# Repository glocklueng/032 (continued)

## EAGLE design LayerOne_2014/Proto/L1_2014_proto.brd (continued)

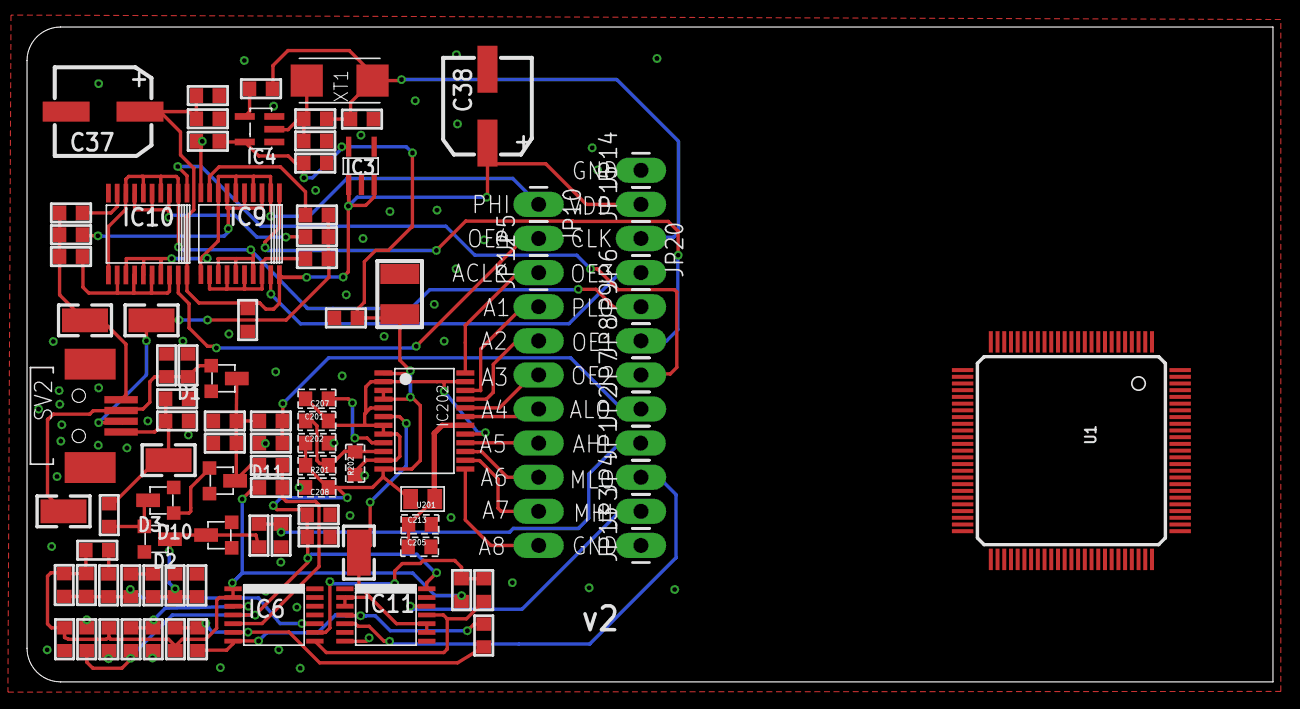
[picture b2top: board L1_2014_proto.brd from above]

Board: 2 copper layers, 92.8 x 48.8 mm, 97 parts (1 on the bottom side), 53 nets.

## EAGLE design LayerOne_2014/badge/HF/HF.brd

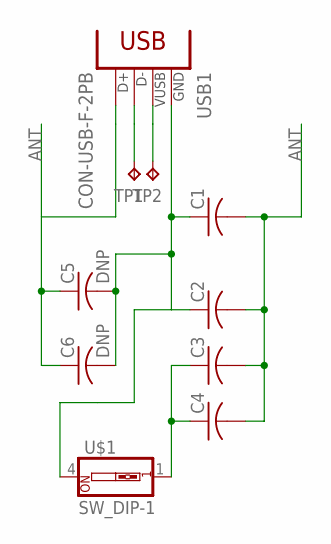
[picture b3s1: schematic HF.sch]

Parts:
C1, C2, C3, C4: C-USC1206; C1206
C5, C6: DNP; C1206
TP1, TP2: TPPAD1-13; P1-13
U$1: SW_DIP-1; DIPSWITCH-01
USB1: CON-USB-F-2PB; CONN_USB_A_F

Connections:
ANT: C1.2, C2.2, C3.2, C4.2, C5.1, C6.1, USB1.3 (D+)
unnamed: C1.1, C2.1, C5.2, C6.2, U$1.4, USB1.4 (GND)
unnamed: C3.1, C4.1, U$1.1
unnamed: TP1.TP, USB1.2 (D-)
unnamed: TP2.TP, USB1.1 (VUSB)

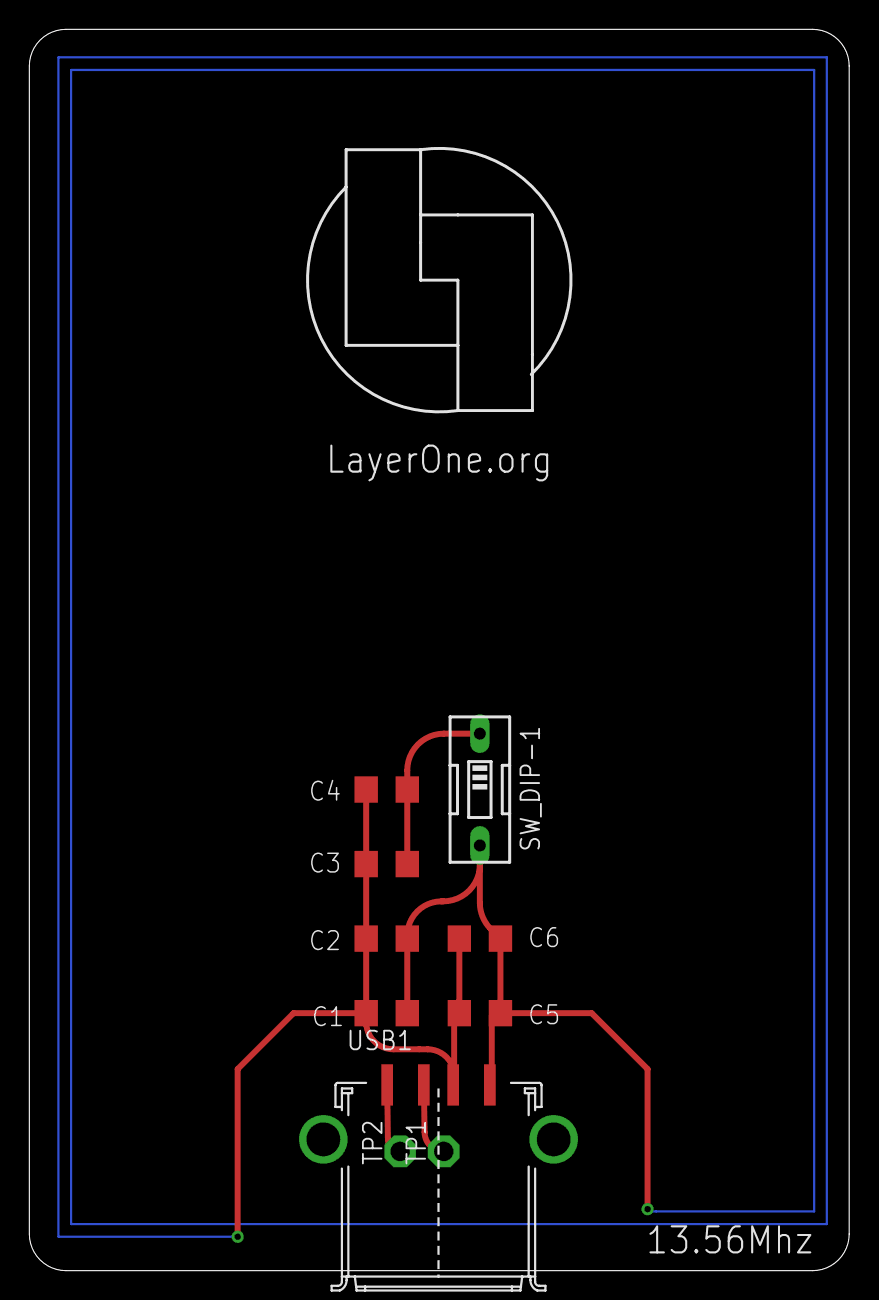
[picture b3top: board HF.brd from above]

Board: 2 copper layers, 55.9 x 84.6 mm, 11 parts (0 on the bottom side), 5 nets.

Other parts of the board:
U$2: LARGE_L1_LOGO

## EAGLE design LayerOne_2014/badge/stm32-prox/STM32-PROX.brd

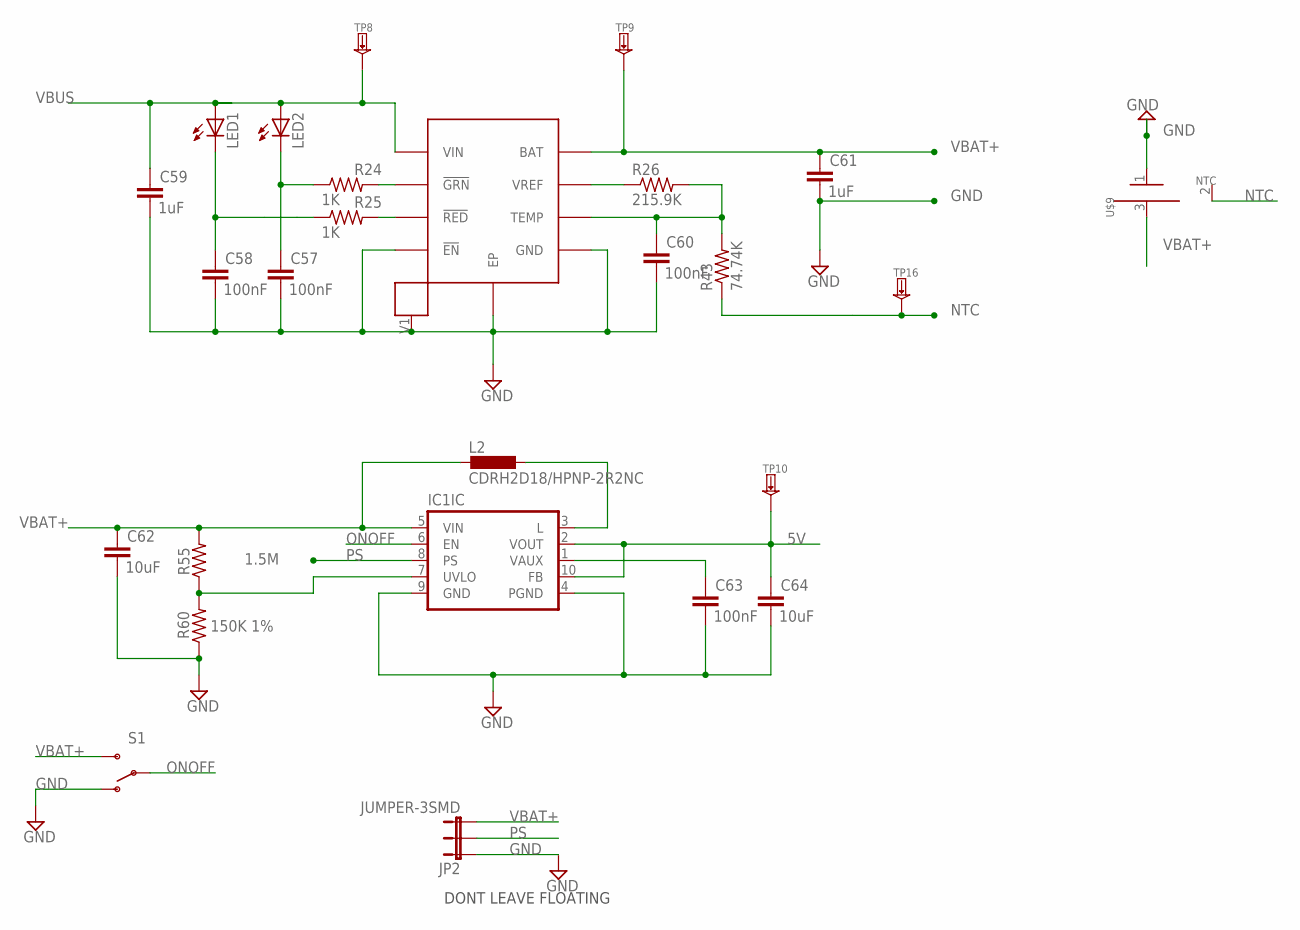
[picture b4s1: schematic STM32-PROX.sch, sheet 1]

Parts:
C57, C58, C60, C63: 100nF; RLC_0603; MPN CL10B104KO8NNNC; DIGIKEY 1276-1005-1-ND
C59, C61: 1uF; RLC_0603; MPN CC0603ZRY5V7BB105; DIGIKEY 311-1372-1-ND
C62, C64: 10uF; RLC_0603; MPN C1608X5R1C106M080AB; DIGIKEY 445-9065-1-ND
IC1: IC_TPS6120XQFN10; QFN-10; MPN TPS61202DRCT; DIGIKEY 296-21685-1-ND
JP2: JUMPER-3SMD; SJ_3; MPN NONE
L2: CDRH2D18/HPNP-2R2NC; CDRH2D18; PARTNO *
LED1: LED_LEDSML0603; LED_SML0603; PARTNO *; DIGIKEY 475-1409-1-ND
LED2: LED_LEDSML0603; LED_SML0603; PARTNO *; DIGIKEY 475-3016-1-ND
R24, R25: 1K; RLC_0603; MPN RMCF0603JT1K00; DIGIKEY RMCF0603JT1K00CT-ND
R26: 215.9K; RLC_0603; MPN CRCW0603215KFKEA; DIGIKEY 541-215KHCT-ND
R43: 74.74K; RLC_0603; MPN RMCF0603JT75K0; DIGIKEY RMCF0603JT75K0CT-ND
R55: 1.5M; RLC_0603; TOLERANCE 5%; MPN ESR03EZPJ155; DIGIKEY RHM1.5MDCT-ND
R60: 150K 1%; RLC_0603; TOLERANCE 1%; MPN ESR03EZPF1503; DIGIKEY RHM150KADCT-ND
S1: SWITCH-SPDT-SMD-A; SWITCH-SPST-SMD-A; PARTNO *
TP8: TESTPADKEYSTONE-SMD; SMD-TESTPOINT; MPN NONE
TP9, TP10: TESTPADKEYSTONE-SMD; --MERGED_KEYSTONE-SMD-TESTPOINT-5015; MPN NONE
TP16: TESTPAD; SMD-TESTPOINT
U$7: MC34674; UDFN-EP; MPN MC34674AEPR2; DIGIKEY MC34674AEPR2TR-ND
U$9: BATT; MPN MC34674AEPR2; DIGIKEY MC34674AEPR2TR-ND

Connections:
5V: C64.1, IC1.2 (VOUT), IC1.10 (FB), TP10.1; also elsewhere on the board
GND: C57.2, C58.2, C59.2, C60.2, C61.2, C62.2, C63.2, C64.2, IC1.4 (PGND), IC1.9 (GND), IC1.P0 (GND), IC1.P1 (GND), IC1.P2 (GND), IC1.P3 (GND), IC1.P4 (GND), IC1.V0 (GND), IC1.V1 (GND), JP2.1, R60.1, S1.1 (O), U$7.4 (!EN), U$7.5 (GND), U$7.9 (EP), U$7.V1, U$9.1 (NEG); also elsewhere on the board
unnamed: C57.1, LED2.C, R24.1
unnamed: R24.2, U$7.2 (!GRN)
unnamed: C58.1, LED1.C, R25.1
unnamed: R25.2, U$7.3 (!RED)
unnamed: R26.1, U$7.7 (VREF)
unnamed: C60.1, R26.2, R43.2, U$7.6 (TEMP)
unnamed: C63.1, IC1.1 (VAUX)
unnamed: IC1.7 (UVLO), R55.1, R60.2
unnamed: IC1.3 (L), L2.P$2 (2)
NTC: R43.1, TP16.1, U$9.2 (NTC)
ONOFF: IC1.6 (EN), S1.2
PS: IC1.8 (PS), JP2.2
VBAT+: C61.1, C62.1, IC1.5 (VIN), JP2.3, L2.P$1 (1), R55.2, S1.3 (S), TP9.1, U$7.8 (BAT), U$9.3 (POS)
VBUS: C59.1, LED1.A, LED2.A, TP8.1, U$7.1 (VIN); also elsewhere on the board

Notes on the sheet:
DONT LEAVE FLOATING

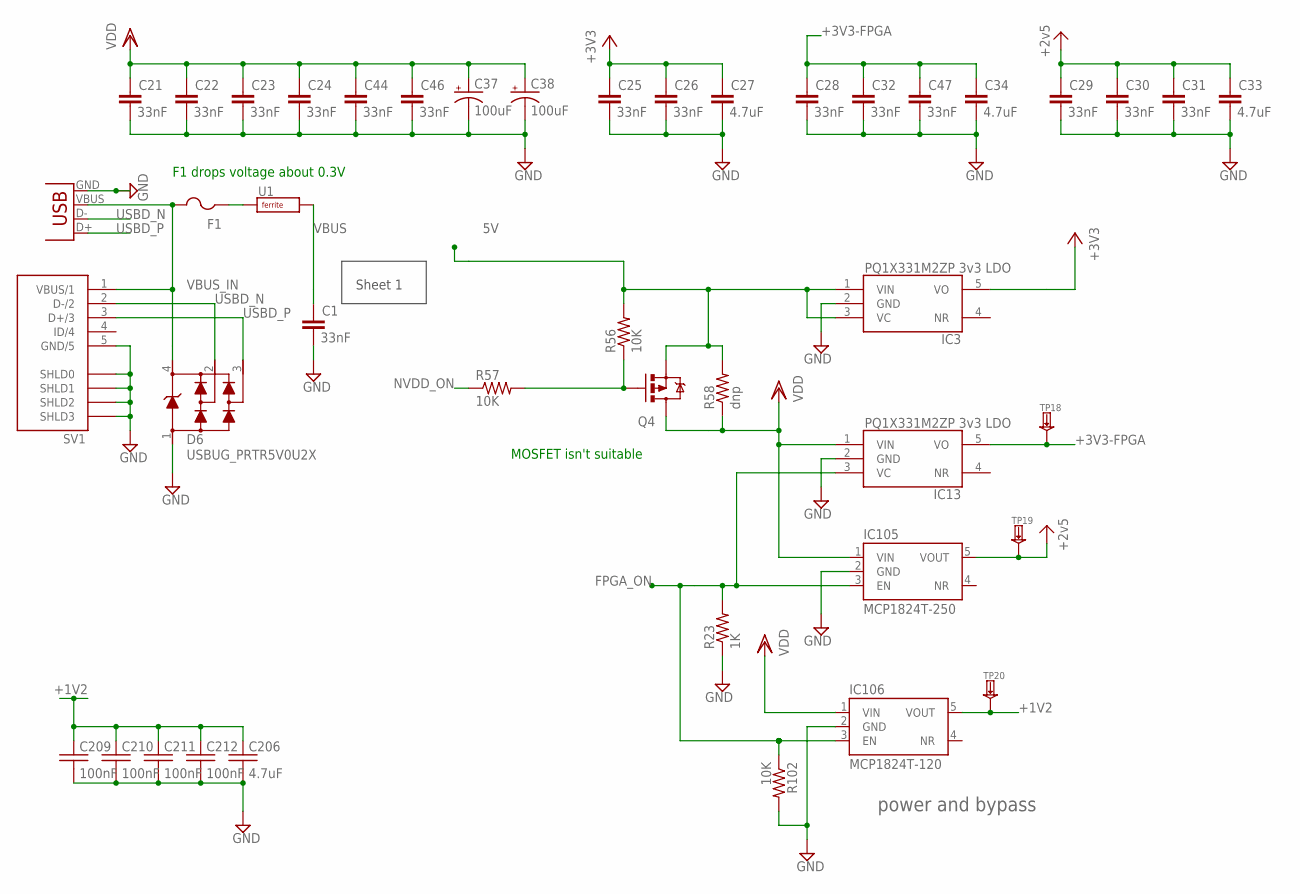
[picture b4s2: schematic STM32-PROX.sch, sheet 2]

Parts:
C1, C21, C22, C23, C24, C25, C26, C28, C29, C30, C31, C32, C44, C46, C47: 33nF; RLC_0603; MPN CC0603KRX7R9BB333; DIGIKEY 311-1429-1-ND
C27, C33, C34: 4.7uF; RLC_1210; MPN CL32B475KOINNNE; DIGIKEY 1276-1856-1-ND
C37, C38: 100uF; D/7343-31R; MPN T491D107K010AT; DIGIKEY 399-3769-1-ND
C206: 4.7uF; RLC_0603; MPN EMK107ABJ475KA-T; DIGIKEY 1276-1784-1-ND
C209, C210, C211, C212: 100nF; RLC_0603; MPN CL10B104KO8NNNC; DIGIKEY 1276-1005-1-ND
D6: USBUG_PRTR5V0U2X; USBUG_SOT143B
F1: PTCFUSE-1812; 1812; MPN MICROSMD050F-2; DIGIKEY MICROSMD050FCT-ND
IC3: PQ1X331M2ZP-3V3-LDO-SOT-23-5; SOT-23-5; MPN LP2985-33DBVR; DIGIKEY 296-18476-1-ND
IC13: PQ1X331M2ZP-3V3-LDO-SOT-23-5; SOT-23-5; MPN LP2985-33DBVR; DIGIKEY 296-18476-2-ND
IC105: MCP1824T-250; SOT-23-5; MPN MCP1824T-2502E/OT; DIGIKEY MCP1824T-2502E/OTCT-ND
IC106: MCP1824T-120; SOT-23-5; MPN MCP1824T-1202E/OT; DIGIKEY MCP1824T-1202E/OTCT-ND
Q4: MOSFET-PCHANNELSMD; SOT23-3; MPN SI2303CDS-T1-GE3; DIGIKEY SI2303CDS-T1-GE3CT-ND
R23: 1K; RLC_0603; MPN RMCF0603JT1K00; DIGIKEY RMCF0603JT1K00CT-ND
R56, R57, R102: 10K; RLC_0603; MPN RMCF0603JT10K0; DIGIKEY RMCF0603JT10K0CT-ND
R58: dnp; RLC_0603; PARTNO *
SV1: USB-MINIB; USB-MINIB-SMD; PARTNO *
TP18, TP19, TP20: TESTPAD; SMD-TESTPOINT
U1: FERRITE0805; RLC_0805; MPN MPZ2012S300A; DIGIKEY 445-1566-1-ND
USB-MICRO: USB-MICROB; MPN 1981568-1; DIGIKEY A97800CT-ND

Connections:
5V: IC3.1 (VIN), IC3.3 (VC), Q4.2 (S), R56.2, R58.2; also elsewhere on the board
+1V2: C206.1, C209.1, C210.1, C211.1, C212.1, IC106.5 (VOUT), TP20.1; also elsewhere on the board
+2V5: C29.1, C30.1, C31.1, C33.1, IC105.5 (VOUT), TP19.1; also elsewhere on the board
+3V3-FPGA: C28.1, C32.1, C34.1, C47.1, IC13.5 (VO), TP18.1; also elsewhere on the board
FPGA_ON: IC13.3 (VC), IC105.3 (EN), IC106.3 (EN), R23.2, R102.1; also elsewhere on the board
GND: C1.2, C21.2, C22.2, C23.2, C24.2, C25.2, C26.2, C27.2, C28.2, C29.2, C30.2, C31.2, C32.2, C33.2, C34.2, C37.-, C38.-, C44.2, C46.2, C47.2, C206.2, C209.2, C210.2, C211.2, C212.2, D6.1, IC3.2 (GND), IC13.2 (GND), IC105.2 (GND), IC106.2 (GND), R23.1, R102.2, SV1.5 (GND/5), SV1.TAB0 (SHLD0), SV1.TAB1 (SHLD1), SV1.TAB2 (SHLD2), SV1.TAB3 (SHLD3), USB-MICRO.GND; also elsewhere on the board
unnamed: F1.1, U1.1 (A)
NVDD_ON: R57.1; also elsewhere on the board
PFETGATE: Q4.1 (G), R56.1, R57.2
USBD_N: D6.2, SV1.2 (D-/2), USB-MICRO.D-; also elsewhere on the board
USBD_P: D6.3, SV1.3 (D+/3), USB-MICRO.D+; also elsewhere on the board
VBUS: C1.1, U1.2 (B); also elsewhere on the board
VBUS_IN: D6.4, F1.2, SV1.1 (VBUS/1), USB-MICRO.VBUS
VCC: C25.1, C26.1, C27.1, IC3.5 (VO); also elsewhere on the board
VDD: C21.1, C22.1, C23.1, C24.1, C37.+, C38.+, C44.1, C46.1, IC13.1 (VIN), IC105.1 (VIN), IC106.1 (VIN), Q4.3 (D), R58.1; also elsewhere on the board

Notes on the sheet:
power and bypass
Sheet 1
F1 drops voltage about 0.3V
MOSFET isn't suitable

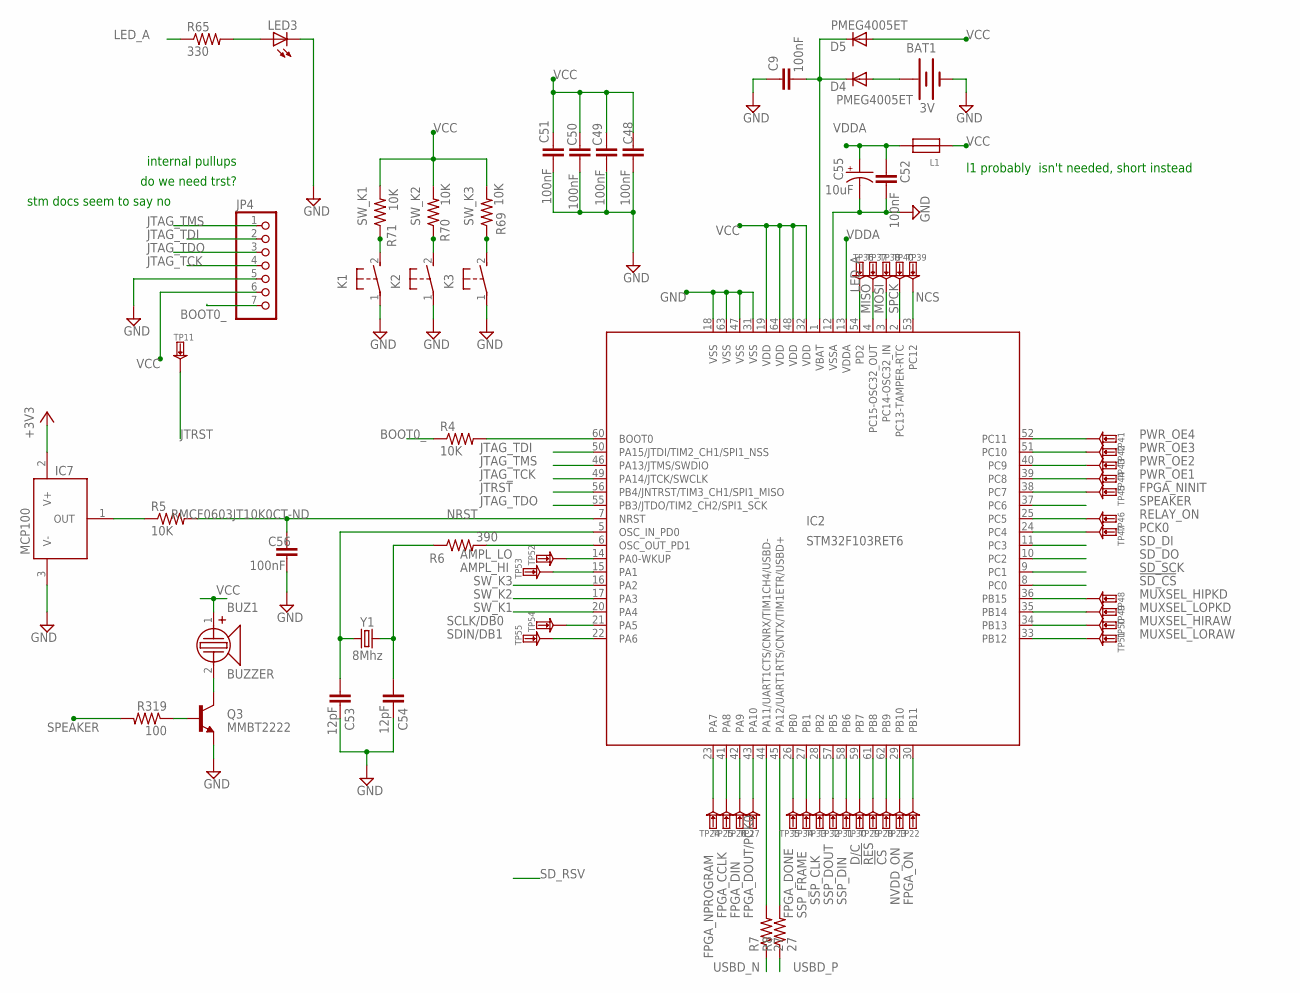
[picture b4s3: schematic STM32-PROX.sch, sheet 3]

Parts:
BAT1: 3V; NSL_SPARKFUN_BATTCON_12MM; MPN BK-885-TR; DIGIKEY BK-885CT-ND
BUZ1: BUZZER; MPN CCV-084B16; DIGIKEY 102-1265-1-ND
C9: 100nF; RLC_0603; MPN CL21F104ZBCNNNC; DIGIKEY 1276-1007-1-ND
C48, C49, C50, C51, C52, C56: 100nF; 0805; MPN CL21F104ZBCNNNC; DIGIKEY 1276-1007-1-ND
C53, C54: 12pF; 0805; MPN CL21C120JBANNNC; DIGIKEY 1276-1120-1-ND
C55: 10uF; EIA3216-KIT; MPN TAJA106M006RNJ; DIGIKEY 478-1656-1-ND
D4, D5: PMEG4005ET; SOT23-3; MPN PMEG4005ET,215; DIGIKEY 568-4134-1-ND
IC2: STM32F103RET6; LQFP64A_PACKAGE; MPN STM32F103RET6; DIGIKEY 497-6444-ND
IC7: MCP100; SOT23-3LEAD; MPN MCP100T-270I/TT; DIGIKEY MCP100T-270I/TTCT-ND
JP4: HEADER-1X7ROUND; 1X07_ROUND
K1, K2, K3: 5-XX; B3F-5XX; MPN PTS635SL50 LFS; DIGIKEY CKN9102-ND
L1: FERRITE1; 0603; MPN NONE
LED3: LED_LEDSML0603; LED_SML0603; PARTNO *; DIGIKEY 475-2558-1-ND
Q3: MMBT2222; SOT-23-3; MPN MMBT2222A-7-F
R4, R5, R69, R70, R71: 10K; RLC_0603; MPN RMCF0603JT10K0; DIGIKEY RMCF0603JT10K0CT-ND
R6: 390; RLC_0603; MPN RMCF0603JT390R; DIGIKEY RMCF0603JT390RCT-ND
R7, R8: 27; RLC_0603; MPN RMCF0603JT27R0; DIGIKEY RMCF0603JT27R0CT-ND
R65: 330; RLC_0603; MPN RMCF0603JT330R; DIGIKEY RMCF0603JT330RCT-ND
R319: 100; RLC_0603; MPN RMCF0603JT100R; DIGIKEY RMCF0603JT100RCT-ND
TP11, TP22, TP23, TP24, TP25, TP26, TP27, TP28, TP29, TP30, TP31, TP32, TP33, TP34, TP35, TP36, TP37, TP38, TP39, TP40, TP41, TP42, TP43, TP44, TP45, TP46, TP47, TP48, TP49, TP50, TP51, TP52, TP53, TP54, TP55: TESTPAD; SMD-TESTPOINT
Y1: 8Mhz; CRYSTAL-TXC-7A; MPN 7A-8.000MAAE-T; DIGIKEY 887-1740-1-ND

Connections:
!CS: IC2.62 (PB9), TP28.1; also elsewhere on the board
!RES: IC2.61 (PB8), TP29.1; also elsewhere on the board
!SD_CS: IC2.8 (PC0); also elsewhere on the board
AMPL_HI: IC2.15 (PA1), TP53.1; also elsewhere on the board
AMPL_LO: IC2.14 (PA0-WKUP), TP52.1; also elsewhere on the board
BOOT0: IC2.60 (BOOT0), R4.2
BOOT0_: JP4.7, R4.1
D/C: IC2.59 (PB7), TP30.1; also elsewhere on the board
D_N: IC2.44 (PA11/UART1CTS/CNRX/TIM1CH4/USBD-), R7.2
D_P: IC2.45 (PA12/UART1RTS/CNTX/TIM1ETR/USBD+), R8.2
FPGA_CCLK: IC2.41 (PA8), TP25.1; also elsewhere on the board
FPGA_DIN: IC2.42 (PA9), TP26.1; also elsewhere on the board
FPGA_DONE: IC2.26 (PB0), TP35.1; also elsewhere on the board
FPGA_DOUT/PCK0: IC2.43 (PA10), TP27.1; also elsewhere on the board
FPGA_NINIT: IC2.38 (PC7), TP45.1; also elsewhere on the board
FPGA_NPROGRAM: IC2.23 (PA7), TP24.1; also elsewhere on the board
FPGA_ON: IC2.30 (PB11), TP22.1; also elsewhere on the board
GND: BAT1.GND (-), C9.1, C48.2, C49.2, C50.2, C51.2, C52.2, C53.1, C54.1, C55.C (-), C56.2, IC2.12 (VSSA), IC2.18 (VSS), IC2.31 (VSS), IC2.47 (VSS), IC2.63 (VSS), IC7.3 (V-), JP4.5, K1.1, K2.1, K3.1, LED3.C, Q3.2 (E); also elsewhere on the board
JTAG_TCK: IC2.49 (PA14/JTCK/SWCLK), JP4.4
JTAG_TDI: IC2.50 (PA15/JTDI/TIM2_CH1/SPI1_NSS), JP4.2
JTAG_TDO: IC2.55 (PB3/JTDO/TIM2_CH2/SPI1_SCK), JP4.3
JTAG_TMS: IC2.46 (PA13/JTMS/SWDIO), JP4.1
JTRST: IC2.56 (PB4/JNTRST/TIM3_CH1/SPI1_MISO), TP11.1
LED3: LED3.A, R65.2
LED_A: IC2.54 (PD2), R65.1, TP36.1
MISO: IC2.4 (PC15-OSC32_OUT), TP37.1; also elsewhere on the board
MOSI: IC2.3 (PC14-OSC32_IN), TP38.1; also elsewhere on the board
MUXSEL_HIPKD: IC2.36 (PB15), TP48.1; also elsewhere on the board
MUXSEL_HIRAW: IC2.34 (PB13), TP50.1; also elsewhere on the board
MUXSEL_LOPKD: IC2.35 (PB14), TP49.1; also elsewhere on the board
MUXSEL_LORAW: IC2.33 (PB12), TP51.1; also elsewhere on the board
unnamed: C53.2, IC2.5 (OSC_IN_PD0), Y1.P$1 (1)
unnamed: C9.2, D4.3 (C), D5.3 (C), IC2.1 (VBAT)
unnamed: BAT1.PWR@1 (+), D4.1 (A)
unnamed: BUZ1.2, Q3.3 (C)
unnamed: Q3.1 (B), R319.1
unnamed: IC2.6 (OSC_OUT_PD1), R6.2
unnamed: C54.2, R6.1, Y1.P$2 (2)
unnamed: IC7.1 (OUT), R5.1
NCS: IC2.53 (PC12), TP39.1; also elsewhere on the board
NRST: C56.1, IC2.7 (NRST), R5.2
NVDD_ON: IC2.29 (PB10), TP23.1; also elsewhere on the board
PCK0: IC2.24 (PC4), TP47.1; also elsewhere on the board
PWR_OE1: IC2.39 (PC8), TP44.1; also elsewhere on the board
PWR_OE2: IC2.40 (PC9), TP43.1; also elsewhere on the board
PWR_OE3: IC2.51 (PC10), TP42.1; also elsewhere on the board
PWR_OE4: IC2.52 (PC11), TP41.1; also elsewhere on the board
RELAY_ON: IC2.25 (PC5), TP46.1; also elsewhere on the board
SCLK/DB0: IC2.21 (PA5), TP54.1; also elsewhere on the board
SDIN/DB1: IC2.22 (PA6), TP55.1; also elsewhere on the board
SD_DI: IC2.11 (PC3); also elsewhere on the board
SD_DO: IC2.10 (PC2); also elsewhere on the board
SD_SCK: IC2.9 (PC1); also elsewhere on the board
SPCK: IC2.2 (PC13-TAMPER-RTC), TP40.1; also elsewhere on the board
SPEAKER: IC2.37 (PC6), R319.2
SSP_CLK: IC2.28 (PB2), TP33.1; also elsewhere on the board
SSP_DIN: IC2.58 (PB6), TP31.1; also elsewhere on the board
SSP_DOUT: IC2.57 (PB5), TP32.1; also elsewhere on the board
SSP_FRAME: IC2.27 (PB1), TP34.1; also elsewhere on the board
SW_K1: IC2.20 (PA4), K1.2 (S), R71.1
SW_K2: IC2.17 (PA3), K2.2 (S), R70.1
SW_K3: IC2.16 (PA2), K3.2 (S), R69.1
USBD_N: R7.1; also elsewhere on the board
USBD_P: R8.1; also elsewhere on the board
VCC: BUZ1.1, C48.1, C49.1, C50.1, C51.1, D5.1 (A), IC2.19 (VDD), IC2.32 (VDD), IC2.48 (VDD), IC2.64 (VDD), IC7.2 (V+), JP4.6, L1.1, R69.2, R70.2, R71.2; also elsewhere on the board
VDDA: C52.1, C55.A (+), IC2.13 (VDDA), L1.2

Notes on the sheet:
do we need trst?
internal pullups
stm docs seem to say no
l1 probably isn't needed, short instead

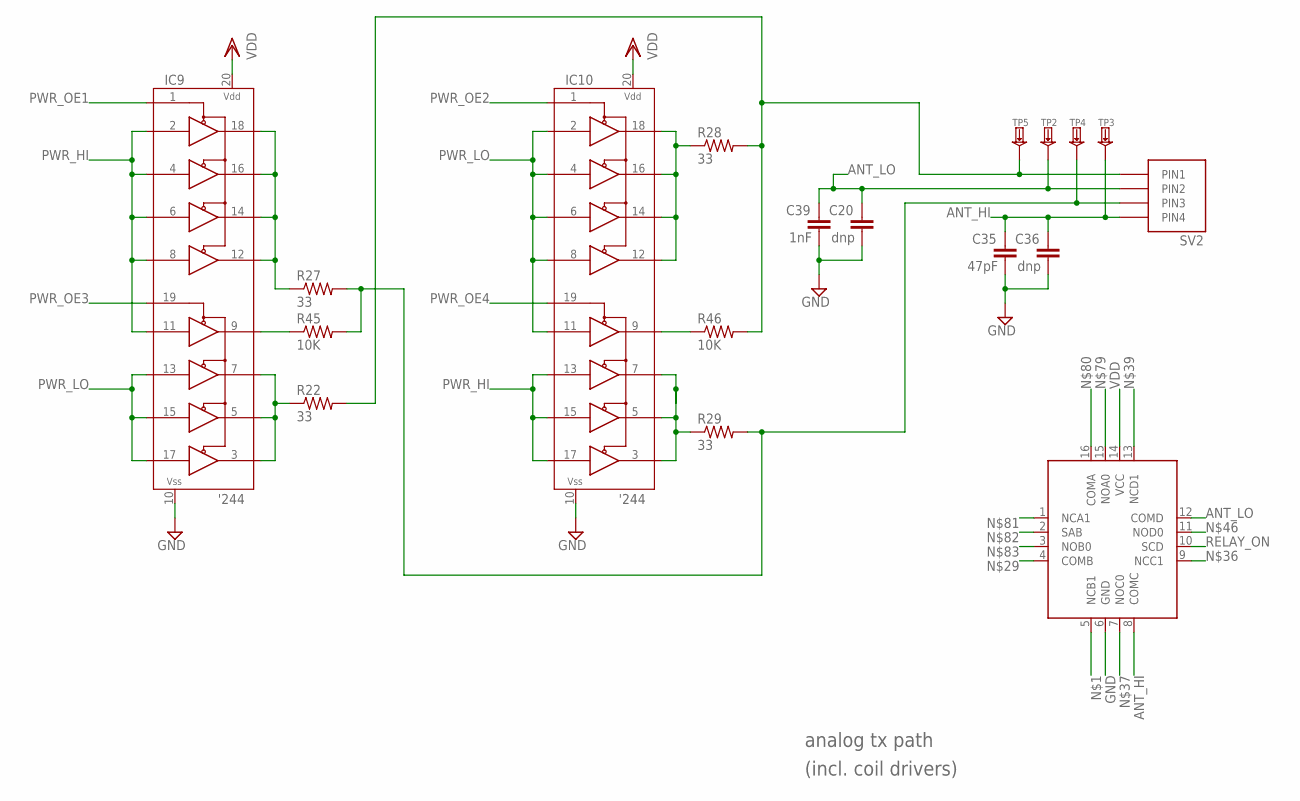
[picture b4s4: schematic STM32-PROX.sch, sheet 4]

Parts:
C20, C36: dnp; RLC_0603; PARTNO *
C35: 47pF; RLC_0603; MPN CL10C470JB8NNNC; DIGIKEY 1276-1037-1-ND
C39: 1nF; RLC_0603; MPN GRM188R71H102KA01D; DIGIKEY 490-1494-2-ND
IC9, IC10: 74XX244; TSSOP-20; MPN 74AC244TTR; DIGIKEY 497-2913-1-ND
IC12: NLAST44599MNG; QFN16; MPN NLAST44599MNG; DIGIKEY NLAST44599MNR2GOSCT-ND
R22, R27, R28, R29: 33; RLC_0603; MPN RC0603JR-0733RL; DIGIKEY 311-33GRTR-ND
R45, R46: 10K; RLC_0603; MPN RMCF0603JT10K0; DIGIKEY RMCF0603JT10K0CT-ND
SV2: HIROSE-MQ172-4POS; PARTNO *; DIGIKEY H10488CT-ND
TP2, TP3, TP4, TP5: TESTPADKEYSTONE-SMD; KEYSTONE-SMD-TESTPOINT-5015; PARTNO *

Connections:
ANT_HI: C35.1, C36.1, IC12.8 (COMC), SV2.4 (PIN4), TP3.1; also elsewhere on the board
ANT_LO: C20.1, C39.1, IC12.12 (COMD), SV2.2 (PIN2), TP2.1; also elsewhere on the board
GND: C20.2, C35.2, C36.2, C39.2, IC9.10 (VSS), IC10.10 (VSS), IC12.6 (GND); also elsewhere on the board
unnamed: R27.2, R29.2, R45.2, SV2.3 (PIN3), TP4.1
unnamed: R22.2, R28.2, R46.2, SV2.1 (PIN1), TP5.1
unnamed: IC9.12 (1Y4), IC9.14 (1Y3), IC9.16 (1Y2), IC9.18 (1Y1), R27.1
unnamed: IC10.12 (1Y4), IC10.14 (1Y3), IC10.16 (1Y2), IC10.18 (1Y1), R28.1
unnamed 94: IC12.9 (NCC1); also elsewhere on the board
unnamed 95: IC12.7 (NOC0); also elsewhere on the board
unnamed 97: IC12.13 (NCD1); also elsewhere on the board
unnamed: IC9.3 (2Y4), IC9.5 (2Y3), IC9.7 (2Y2), R22.1
unnamed: IC10.3 (2Y4), IC10.5 (2Y3), IC10.7 (2Y2), R29.1
unnamed: IC9.9 (2Y1), R45.1
unnamed: IC10.9 (2Y1), R46.1
unnamed 104: IC12.11 (NOD0); also elsewhere on the board
PWR_HI: IC9.2 (1A1), IC9.4 (1A2), IC9.6 (1A3), IC9.8 (1A4), IC9.11 (2A1), IC10.13 (2A2), IC10.15 (2A3), IC10.17 (2A4); also elsewhere on the board
PWR_LO: IC9.13 (2A2), IC9.15 (2A3), IC9.17 (2A4), IC10.2 (1A1), IC10.4 (1A2), IC10.6 (1A3), IC10.8 (1A4), IC10.11 (2A1); also elsewhere on the board
PWR_OE1: IC9.1 (1NOE); also elsewhere on the board
PWR_OE2: IC10.1 (1NOE); also elsewhere on the board
PWR_OE3: IC9.19 (2NOE); also elsewhere on the board
PWR_OE4: IC10.19 (2NOE); also elsewhere on the board
RELAY_ON: IC12.10 (SCD); also elsewhere on the board
VDD: IC9.20 (VDD), IC10.20 (VDD), IC12.14 (VCC); also elsewhere on the board

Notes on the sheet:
analog tx path
(incl. coil drivers)

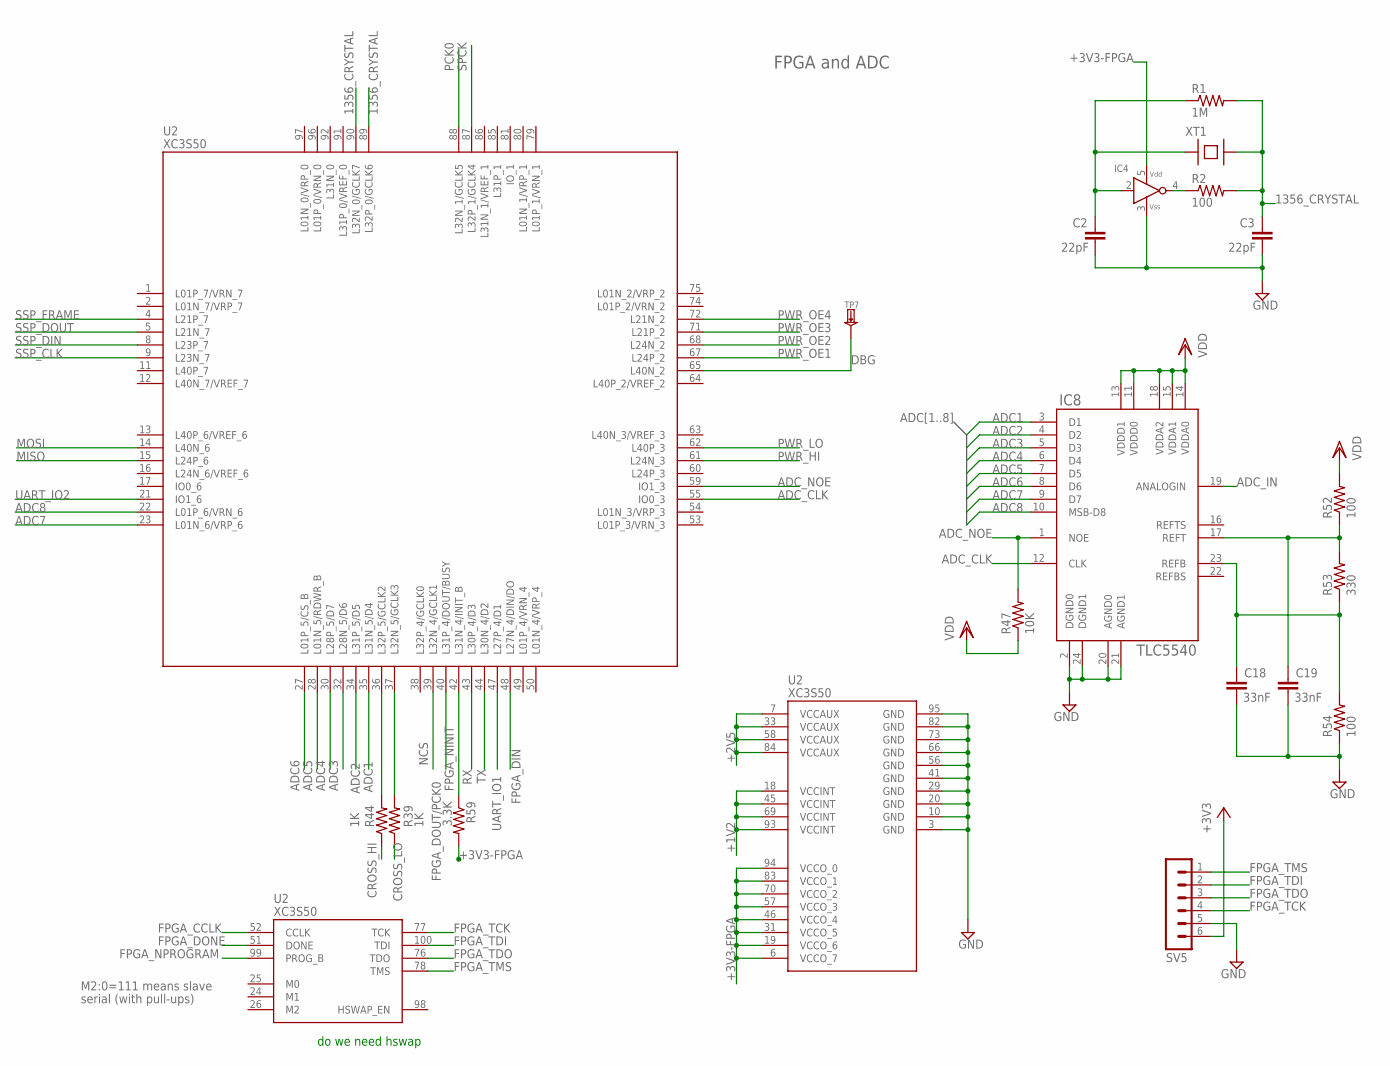
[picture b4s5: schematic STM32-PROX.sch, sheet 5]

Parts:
C2, C3: 22pF; RLC_0603; MPN C1608C0G1H220J080AA; DIGIKEY 445-1273-1-ND
C18, C19: 33nF; RLC_0603; MPN CC0603KRX7R9BB333; DIGIKEY 311-1429-1-ND
IC4: HCU-INVERTER; SMV-5; PARTNO *; DIGIKEY NC7SZ04M5XCT-ND
IC8: TLC5540; TSSOP-24; MPN TLC5540IPW; DIGIKEY 296-2184-5-ND
R1: 1M; RLC_0603; MPN RC0603JR-071ML; DIGIKEY 311-1.0MGRTR-ND
R2, R52, R54: 100; RLC_0603; MPN RMCF0603JT100R; DIGIKEY RMCF0603JT100RCT-ND
R39, R44: 1K; RLC_0603; MPN RMCF0603JT1K00; DIGIKEY RMCF0603JT1K00CT-ND
R47: 10K; RLC_0603; MPN RMCF0603JT10K0; DIGIKEY RMCF0603JT10K0CT-ND
R53: 330; RLC_0603; MPN RMCF0603JT330R; DIGIKEY RMCF0603JT330RCT-ND
R59: 3.3K; RLC_0603; MPN RMCF0603JT3K30; DIGIKEY RMCF0603JT3K30CT-ND
SV5: HEADER-MALE-6X1; HEADER-MALE-6X1-0.100-UNKEYED; PARTNO *
TP7: TESTPADKEYSTONE-SMD; KEYSTONE-SMD-TESTPOINT-5015; PARTNO *
U2: XC3S50; VQ100; MPN XC3S50-5VQ100C (not on bom)
XT1: XTAL-SMD-CITIZEN-CS10; MPN ABM3-13.560MHZ-B2-T; DIGIKEY 535-9101-1-ND

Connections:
1356_CRYSTAL: C3.1, R1.2, R2.2, U2.89 (L32P_0/GCLK6), U2.90 (L32N_0/GCLK7), XT1.B
+1V2: U2.18 (VCCINT), U2.45 (VCCINT), U2.69 (VCCINT), U2.93 (VCCINT); also elsewhere on the board
+2V5: U2.7 (VCCAUX), U2.33 (VCCAUX), U2.58 (VCCAUX), U2.84 (VCCAUX); also elsewhere on the board
+3V3-FPGA: IC4.5 (VDD), R59.2, U2.6 (VCCO_7), U2.19 (VCCO_6), U2.31 (VCCO_5), U2.46 (VCCO_4), U2.57 (VCCO_3), U2.70 (VCCO_2), U2.83 (VCCO_1), U2.94 (VCCO_0); also elsewhere on the board
ADC1: IC8.3 (D1), U2.35 (L31N_5/D4)
ADC2: IC8.4 (D2), U2.34 (L31P_5/D5)
ADC3: IC8.5 (D3), U2.32 (L28N_5/D6)
ADC4: IC8.6 (D4), U2.30 (L28P_5/D7)
ADC5: IC8.7 (D5), U2.28 (L01N_5/RDWR_B)
ADC6: IC8.8 (D6), U2.27 (L01P_5/CS_B)
ADC7: IC8.9 (D7), U2.23 (L01N_6/VRP_6)
ADC8: IC8.10 (MSB-D8), U2.22 (L01P_6/VRN_6)
ADC_CLK: IC8.12 (CLK), U2.55 (IO0_3)
ADC_IN: IC8.19 (ANALOGIN); also elsewhere on the board
ADC_NOE: IC8.1 (NOE), R47.2, U2.59 (IO1_3)
CROSS_HI: R44.1; also elsewhere on the board
CROSS_LO: R39.1; also elsewhere on the board
DBG: TP7.1, U2.65 (L40N_2)
FPGA_CCLK: U2.52 (CCLK); also elsewhere on the board
FPGA_DIN: U2.48 (L27N_4/DIN/DO); also elsewhere on the board
FPGA_DONE: U2.51 (DONE); also elsewhere on the board
FPGA_DOUT/PCK0: U2.40 (L31P_4/DOUT/BUSY); also elsewhere on the board
FPGA_NINIT: R59.1, U2.42 (L31N_4/INIT_B); also elsewhere on the board
FPGA_NPROGRAM: U2.99 (PROG_B); also elsewhere on the board
FPGA_TCK: SV5.4, U2.77 (TCK)
FPGA_TDI: SV5.2, U2.100 (TDI)
FPGA_TDO: SV5.3, U2.76 (TDO)
FPGA_TMS: SV5.1, U2.78 (TMS)
GND: C2.2, C3.2, C18.2, C19.2, IC4.3 (VSS), IC8.2 (DGND0), IC8.20 (AGND0), IC8.21 (AGND1), IC8.24 (DGND1), R54.1, SV5.5, U2.3 (GND), U2.10 (GND), U2.20 (GND), U2.29 (GND), U2.41 (GND), U2.56 (GND), U2.66 (GND), U2.73 (GND), U2.82 (GND), U2.95 (GND); also elsewhere on the board
MISO: U2.15 (L24P_6); also elsewhere on the board
MOSI: U2.14 (L40N_6); also elsewhere on the board
unnamed: IC4.4 (Y), R2.1
unnamed: C2.1, IC4.2 (A), R1.1, XT1.A
unnamed: C18.1, IC8.23 (REFB), R53.1, R54.2
unnamed: R39.2, U2.37 (L32N_5/GCLK3)
unnamed: R44.2, U2.36 (L32P_5/GCLK2)
unnamed: C19.1, IC8.17 (REFT), R52.1, R53.2
NCS: U2.39 (L32N_4/GCLK1); also elsewhere on the board
PCK0: U2.88 (L32N_1/GCLK5); also elsewhere on the board
PWR_HI: U2.61 (L24N_3); also elsewhere on the board
PWR_LO: U2.62 (L40P_3); also elsewhere on the board
PWR_OE1: U2.67 (L24P_2); also elsewhere on the board
PWR_OE2: U2.68 (L24N_2); also elsewhere on the board
PWR_OE3: U2.71 (L21P_2); also elsewhere on the board
PWR_OE4: U2.72 (L21N_2); also elsewhere on the board
RX: U2.43 (L30P_4/D3)
SPCK: U2.87 (L32P_1/GCLK4); also elsewhere on the board
SSP_CLK: U2.9 (L23N_7); also elsewhere on the board
SSP_DIN: U2.8 (L23P_7); also elsewhere on the board
SSP_DOUT: U2.5 (L21N_7); also elsewhere on the board
SSP_FRAME: U2.4 (L21P_7); also elsewhere on the board
TX: U2.44 (L30N_4/D2)
UART_IO1: U2.47 (L27P_4/D1)
UART_IO2: U2.21 (IO1_6)
VCC: SV5.6; also elsewhere on the board
VDD: IC8.11 (VDDD0), IC8.13 (VDDD1), IC8.14 (VDDA0), IC8.15 (VDDA1), IC8.18 (VDDA2), R47.1, R52.2; also elsewhere on the board

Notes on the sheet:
FPGA and ADC
M2:0=111 means slave
serial (with pull-ups)
do we need hswap

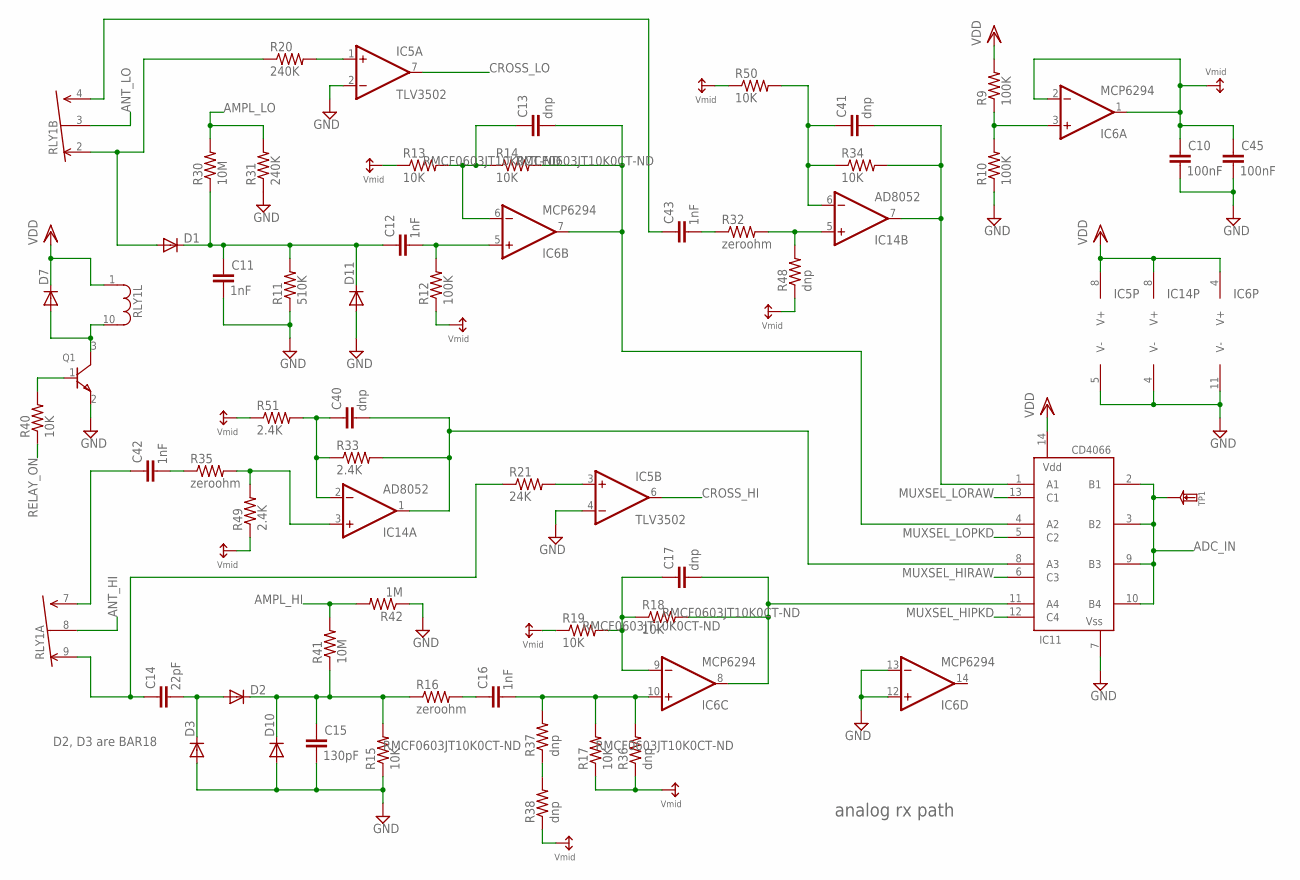
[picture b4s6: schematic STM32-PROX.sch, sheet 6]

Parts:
C10, C45: 100nF; RLC_0603; MPN CL10B104KO8NNNC; DIGIKEY 1276-1005-1-ND
C11, C12, C16, C42, C43: 1nF; RLC_0603; MPN GRM188R71H102KA01D; DIGIKEY 490-1494-2-ND
C13, C17, C40, C41: dnp; RLC_0603; PARTNO *
C14: 22pF; RLC_0603; MPN C1608C0G1H220J080AA; DIGIKEY 445-1273-1-ND
C15: 130pF; RLC_0603; MPN GRM1885C1H131JA01D; DIGIKEY 490-1430-1-ND
D1, D2, D3: DIODE-SMD-SOT23; SOT23-3LEAD; MPN BAS 21 E6327; DIGIKEY BAS21INCT-ND
D7: DIODE-SMD-SOT23; SOT23-3LEAD; PARTNO *; DIGIKEY BZX84C47-FDICT-ND
D10, D11: DIODE-SMD-SOT23; SOT23-3LEAD; PARTNO *
IC5: TLV3502; SOT-23-8-OR-MSOP-8; MPN TLV3502AIDCNT; DIGIKEY 296-18147-1-ND
IC6: MCP6294; TSSOP-14; MPN MCP6294-E/ST; DIGIKEY MCP6294-E/ST-ND
IC11: CD4066; TSSOP-14; MPN CD4066BPWR; DIGIKEY 296-14123-1-ND
IC14: AD8052; MSOP8; MPN AD8052ARMZ; DIGIKEY AD8052ARMZ-ND
Q1: NPN-SOT23-2N3904; SOT23-3LEAD; MPN PMBT3904,215; DIGIKEY 568-1741-1-ND
R9, R10, R12: 100K; RLC_0603; MPN RC0603JR-07100KL; DIGIKEY 311-100KGRTR-ND
R11: 510K; RLC_0603; MPN ERJ-3GEYJ514V; DIGIKEY P510KGTR-ND
R13, R14, R15, R17, R18, R19, R34, R40, R50: 10K; RLC_0603; MPN RMCF0603JT10K0; DIGIKEY RMCF0603JT10K0CT-ND
R16, R32, R35: zeroohm; RLC_0603; PARTNO *
R20, R31: 240K; RLC_0603; MPN RC1608J244CS; DIGIKEY 1276-5119-2-ND
R21: 24K; RLC_0603; MPN RC0603JR-0724KL; DIGIKEY 311-24KGRTR-ND
R30, R41: 10M; RLC_0603; MPN RC0603JR-0710ML; DIGIKEY 311-10MGRTR-ND
R33, R49, R51: 2.4K; RLC_0603; MPN RC0603FR-072K4L; DIGIKEY 311-2.40KHRTR-ND
R36, R37, R38, R48: dnp; RLC_0603; PARTNO *
R42: 1M; RLC_0603; MPN RC0603JR-071ML; DIGIKEY 311-1.0MGRTR-ND
RLY1: RELAY-DPDT; TQ-SMD-RELAY; PARTNO *
TP1: TESTPAD; SMD-TESTPOINT; PARTNO *

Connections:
ADCDR_HI: C17.2, IC6.8 (OUT), IC11.11 (A4), R18.2
ADCDR_LO: C13.2, IC6.7 (OUT), IC11.4 (A2), R14.2
ADC_IN: IC11.2 (B1), IC11.3 (B2), IC11.9 (B3), IC11.10 (B4), TP1.1; also elsewhere on the board
AMPL_HI: R41.2, R42.2; also elsewhere on the board
AMPL_LO: R30.2, R31.2; also elsewhere on the board
ANT_HI: RLY1.8 (COM); also elsewhere on the board
ANT_LO: RLY1.3 (COM); also elsewhere on the board
CROSS_HI: IC5.6 (OUT); also elsewhere on the board
CROSS_LO: IC5.7 (OUT); also elsewhere on the board
GND: C10.2, C11.2, C15.2, C45.2, D3.1 (A), D10.1 (A), D11.1 (A), IC5.2 (-IN), IC5.4 (-IN), IC5.5 (V-), IC6.11 (V-), IC6.12 (+IN), IC6.13 (-IN), IC11.7 (VSS), IC14.4 (V-), Q1.2 (E), R10.1, R11.1, R15.1, R31.1, R42.1; also elsewhere on the board
MUXSEL_HIPKD: IC11.12 (C4); also elsewhere on the board
MUXSEL_HIRAW: IC11.6 (C3); also elsewhere on the board
MUXSEL_LOPKD: IC11.5 (C2); also elsewhere on the board
MUXSEL_LORAW: IC11.13 (C1); also elsewhere on the board
unnamed: IC6.3 (+IN), R9.1, R10.2
unnamed: C17.1, IC6.9 (-IN), R18.1, R19.2
unnamed: C12.2, IC6.5 (+IN), R12.2
unnamed: C13.1, IC6.6 (-IN), R13.2, R14.1
unnamed: C16.1, R16.2
unnamed: C11.1, C12.1, D1.3 (C), D11.3 (C), R11.2, R30.1
unnamed: C14.2, D2.1 (A), D3.3 (C)
unnamed: C15.1, D2.3 (C), D10.3 (C), R15.2, R16.1, R41.1
unnamed: C16.2, IC6.10 (+IN), R17.2, R36.2, R37.2
unnamed: IC5.1 (+IN), R20.2
unnamed: IC5.3 (+IN), R21.2
unnamed: D7.1 (A), Q1.3 (C), RLY1.10
unnamed 94: C14.1, R21.1, RLY1.9 (NC); also elsewhere on the board
unnamed 95: C42.1, RLY1.7 (NO); also elsewhere on the board
unnamed: Q1.1 (B), R40.2
unnamed 97: D1.1 (A), R20.1, RLY1.2 (NC); also elsewhere on the board
unnamed: C41.2, IC11.1 (A1), IC14.7 (OUT), R34.2
unnamed 104: C43.1, RLY1.4 (NO); also elsewhere on the board
unnamed: IC14.3 (+IN), R35.2, R49.2
unnamed: C43.2, R32.1
unnamed: C42.2, R35.1
unnamed: C40.1, IC14.2 (-IN), R33.1, R51.2
unnamed: C41.1, IC14.6 (-IN), R34.1, R50.2
unnamed: IC14.5 (+IN), R32.2, R48.2
unnamed: R37.1, R38.2
RAW_HI: C40.2, IC11.8 (A3), IC14.1 (OUT), R33.2
RELAY_ON: R40.1; also elsewhere on the board
VDD: D7.3 (C), IC5.8 (V+), IC6.4 (V+), IC11.14 (VDD), IC14.8 (V+), R9.2, RLY1.1; also elsewhere on the board
VMID: C10.1, C45.1, IC6.1 (OUT), IC6.2 (-IN), R12.1, R13.1, R17.1, R19.1, R36.1, R38.1, R48.1, R49.1, R50.1, R51.1

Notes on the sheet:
analog rx path
D2, D3 are BAR18
